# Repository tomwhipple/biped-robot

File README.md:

# Biped

A ~46 cm (to the deck; 56 cm to the top of the head) 3D-printed **bipedal
robot**: 17 serial-bus servos — six per leg, a neck, and two 2-DOF arms that
push it back up after a fall — an ESP32 running the 50 Hz control loop, and a
Raspberry Pi with a head camera. It is designed to walk by lifting a foot
clear of the ground: a static single-foot stance exists with 30 mm of margin,
and an open-loop gait in simulation, run against the measured actuation chain,
proves the body has the margins. The robot itself is driven by a
reinforcement-learning policy on the ESP32: standing, balance, stepping,
turning and walking all come from it.

**Status:** the legs are built (the 12 leg servos and the control board; no
pack, Pi, head, neck or arms yet), and a trained legs policy —
`robot_legs_walk16_act_s128r24`, a distilled (128, 128) student on the v6 legs
plant — runs on the ESP32 and holds the robot standing. Walking on the floor
is not yet shown on hardware; the milestones are marching in place with full
weight transfer, then a stride, then the full command volume. The CAD for the whole robot is complete and
passes its swept-ROM interference gate; the design passes simulation Gates
A–D, and walking and get-ups train on the robot's plants.
Where everything stands: [DESIGN.md](DESIGN.md) §12–13 and the GitHub issues.

*Loosely inspired by the [Bimo Project](https://github.com/mekion/the-bimo-project);
an independent design built from servo datasheet dimensions, not reverse-engineered
parts.*

## Try it

Everything below runs on a laptop with no robot and no GPU.

```bash
python -m venv .venv && source .venv/bin/activate    # direnv does this via .envrc
pip install -r requirements.txt
make help                                  # every build, run and test target

# look at the robot: drag its joints under gravity, push it over (native Qt window)
make puppet                                # standing; ARGS="--pose supine" or "--pose prone"
make sim                                   # the plant in MuJoCo's viewer

# the design gates, on the robot's plant
python sim/static_gait.py --render build/v6/movies/walk.mp4   # the open-loop walk
python sim/gate_no3250.py walk             # the walk across the gate cases

# regenerate the printable parts from the parametric source, then gate them
make cad                                   # every part whose source changed: STL (build/v6/stl), STEP and mass rollup (build/v6)
make check-cad                             # swept-ROM interference, must PASS
make slice                                 # OrcaSlicer projects + gcode, in build/v6/gcode

# the test gates (also run by the pre-push hook)
make test                                  # the firmware's pure modules under ASan/UBSan + the consoles, then
                                           # pytest tests/ (~4 min) and the SIL suite
```

The console drives a simulated robot over the real command protocol, and
`make console ARGS="--host <robot-ip>"` drives a real one:

```bash
brew install glfw && make console
#   SIM: pick a run, Start; [a] arm, arrows to walk, PgUp/PgDn to turn
```

That is `bimo_gui` (Dear ImGui), the console for hardware sessions. The Qt
operator console that replaces it, `link/bimo_console.py` (built by
`make -C firmware/host console`), opens with `make qtconsole`; it has not yet
run a hardware session ([docs/console.md](docs/console.md)).

**Trained policies are not in the repo.** They are local artifacts under
`sim/runs/` (gitignored); [docs/training.md](docs/training.md) walks the pipeline
from the physics model to the weights compiled into the firmware. Training
wants an NVIDIA GPU; the referee, distillation and export run on a laptop.

## Where to read next

| | |
|---|---|
| [DESIGN.md](DESIGN.md) | **the design**: requirements, kinematics, servos, body, get-up, validation, open decisions, build sequence |
| [cad/README.md](cad/README.md) · [cad/PRINT_LIST.md](cad/PRINT_LIST.md) | the parametric CAD, and what to print and how |
| [docs/bom.md](docs/bom.md) · [docs/assembly.md](docs/assembly.md) | what to buy, and how to put it together |
| [docs/wiring.md](docs/wiring.md) · [docs/servo-map.md](docs/servo-map.md) · [docs/bringup.md](docs/bringup.md) | power and electrical, servo IDs and calibration, bare board to first arm |
| [firmware/README.md](firmware/README.md) · [docs/firmware-design.md](docs/firmware-design.md) | what runs on the ESP32 |
| [docs/control-channel.md](docs/control-channel.md) | the wireless command protocol and its failsafe |
| [docs/console.md](docs/console.md) | the Qt operator console: roles, the stops, input, the tabs, the gamepad, its ports |
| [docs/wifi-cli.md](docs/wifi-cli.md) | the bench CLI over Wi-Fi: provisioning, what is refused, the threat model |
| [docs/training.md](docs/training.md) · [docs/sil-harness.md](docs/sil-harness.md) | how a policy is trained, refereed and deployed |
| [AGENTS.md](AGENTS.md) | working practices: gates, branching, generated files, bench safety |
| [docs/design-v6/](docs/design-v6/README.md) | dated design records and the evidence behind DESIGN.md's numbers |
| [docs/archive/](docs/archive/README.md) | the project's history: the prototype, lessons learned, earlier studies |

## What's in here

```
cad/v6/     the robot's parametric CAD (build123d); cad/v6/dimensions_v6.py is the source of truth
cad/        shared CAD library (cad/common/), slicing and checks
sim/        the plants, design gates, open-loop gait and get-up; the CPU env (referee); sim/mjx/ (GPU training); sim/sil/
firmware/   the ESP32 target: the 50 Hz control loop, and its host test build
link/       the command channel: wire protocol, consoles, bench probes
tools/      sim <-> firmware exporters, and instruments that measure servos and the IMU
infra/      nightly training on the GPU box, burst compute
docs/       build, electrical, software and design records
```

## Hardware

15 × Feetech STS3215 (12 V) + 2 × STS3250 (hip rolls) · Waveshare General
Driver for Robots (ESP32, onboard IMU) · Raspberry Pi 4B + Camera Module 3 Wide · 3S 2200–2600 mAh LiPo ·
PETG prints + silicone rubber soles. Full list: [docs/bom.md](docs/bom.md).

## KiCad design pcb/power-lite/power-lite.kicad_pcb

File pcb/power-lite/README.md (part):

# Power lite: the robot's battery protection and power distribution

*The choices behind it are in
[2026-11-02-power-lite-options.md](../../docs/design-v6/2026-11-02-power-lite-options.md). It
is how the robot is powered. How to solder and wire it: [assembly.md](assembly.md); its
connectors and cables: [harness.md](harness.md).*

A 2-layer board, 97 × 64.5 mm, with through-hole parts only, soldered by hand. It carries:
- the pack's connectors;
- the solder pads for an off-the-shelf 3S BMS and for the main switch;
- the fuses;
- a relay that the E-stop drops;
- the servo distribution;
- the signals to the ESP32.

## How power flows

*The circuit as a wired drawing: `tools/draw_circuit.py`, with the same parts and nets as
`tools/parts.py`. The KiCad schematic carries the same nets as labels on every pin.*

```
pack XT60 (J1) ─ BMS (W1-W5, cuts the negative lead) ─ main switch (W6/W7) ─┬─ F2 3 A ─ J3 ─ General Driver H1 (and the Pi)
pack balance lead (J2) ─ BMS cell taps                                      ├─ F2 3 A ─ J11 E-stop NC ─ K1 coil ─ Q1 ─ GND
                                                                             └─ F1 15 A ─ K1 contact ─ SERVO+ ─ J4-J7
```

- **The BMS** is a ShillehTek CF-3SJH25A-C ($6.99, ships from the US).
  - It sits on wires: its B−, B3, B2 and B1+ pads go to W1, W3, W4 and W5, and its P− pad to
    W2.
  - It switches the negative lead, so the system ground is its P−. The pack's balance lead
    goes only to the BMS, through J2.
  - Its thresholds are not documented. **On the bench it has no under-voltage cut-off**: its
    output stayed on down to 2.13 V a cell
    ([2026-11-19 record](../../docs/design-v6/2026-11-19-power-lite-bms-bench.md)). So it does
    not protect the pack if the robot is left on, and a replacement is open (#207).
- **The main switch** is a 20 A panel toggle on W6 and W7, in the power bay's switch pod
  (#213). It is marked 20 A 125 VAC, with no DC rating: carrying 15 A is within it, but
  breaking DC under load is not rated. So turn it off only after the E-stop has dropped the
  servo rail, and it breaks only the logic's 1 A or so.
- **The servo rail** is fed through the TE 1-1414610-0 relay (K1; 70 A, operates at 7.2 V).
  - The relay's coil current, about 0.13 A, flows only while the E-stop's NC contact (J11) is
    closed and the ESP32 holds `SERVO_EN` high.
  - Pressing the E-stop drops the rail without firmware.
  - Until the ESP32 drives `SERVO_EN`, R2 holds Q1 off and the rail stays off.
- **The coil:** D1 clamps its turn-off. The relay's built-in 470 Ω alone would put about 63 V
  on Q1 (rated 40 V), and about −66 V on the E-stop and Q2's base when the E-stop opens.
  - TE warns that a coil diode slows the release and shortens the contact life (V23134 notes
    4 and 6).
  - The relay switches a few times a session, far inside its 10⁵-operation life, and the
    simulated release still takes only 5.3 ms.
- **The General Driver and the Pi** are fed through F2 and stay up through an E-stop.
- **Surge:** D2 and D3 (1.5KE16A) clamp the servo rail and the switched input. C1 (1000 µF)
  is the servo bulk.

## Connectors

| ref | what | part | pins |
|---|---|---|---|
| J1 | the pack | Amass XT60PW-M | 1 B− (angled side), 2 B+ |
| J2 | the pack's balance lead | JST B4B-XH-A | 1 B−, 2 cell 1+, 3 cell 2+, 4 B+ |
| J3 | General Driver H1 | JST B2B-XH-A | 1 LOGIC (+), 2 GND; the lead runs pin 1 to pin 1 |
| J4–J7 | servo branches: R leg, R upper, L leg, L upper | Molex 22-03-5035 | 1 data, 2 SERVO+, 3 GND (the General Driver's H5 order, "D V G"); data at the housing's bevelled corner, as on H5 |
| J8 | servo data from the General Driver's H5 | Molex 22-03-5035 | 1 data, 2 unconnected, 3 GND; data at the bevelled corner |
| J11 | the E-stop's NC contact | JST B2B-PH-K-S | 1 LOGIC, 2 to K1's coil; any latching switch (0.13 A) |
| J12 | control to the ESP32 | JST B8B-PH-K-S | 2 `SERVO_EN` (IO16), 3 GND, 5 `RAIL_V` (GPIO34), 6 `ESTOP_N` (IO4, with its internal pull-up on); 1, 4, 7, 8 unconnected |
| W1–W5 | the BMS | wire pads | W1 B−, W2 P− (system GND), W3 B3, W4 B2, W5 B1+ |
| W6/W7 | the main switch | wire pads | W6 pack B+, W7 switched (VIN) |

- **J1's plug faces out of the left edge.** The XT60's mating face overhangs the edge by 0.25 mm,
  with its pins 16.1 mm in. Ask the board house for no rail or panel on
  that edge.
- **J3 and J11 are different families** (XH and PH), so the two 2-pin leads cannot swap.
- **The ESP32's readings:**
  - `RAIL_V` is SERVO+ divided by 5.7, giving 2.21 V at 12.6 V.
  - `ESTOP_N` is an open collector (Q2), read by IO4 with its internal pull-up on.
    - It reads low while the E-stop is released, because Q2 conducts while the coil supply is up.
    - It reads high when the E-stop is pressed, the board is unpowered, F2 has blown, or the
      lead is unplugged. Every failure reads as stop.
  - C2 (100 nF) filters `RAIL_V` for the ADC.
- **J3 and J4–J8 follow the General Driver's pin orders**: the cables and checks P1–P4 are in
  [harness.md](harness.md).
- **J4–J8 are keyed like H5.** A stock servo lead joins its two housings' bevelled corners, and
  H5's D is at its bevelled corner, so each header's bevelled corner is at pin 1 (data). The
  board's footprint (`power-lite.pretty/Molex_SPOX_5267-03A_1x03_P2.50mm_Vertical_KeyPin1`) is
  KiCad's stock Mini-SPOX with the housing turned 180° on the same pads.

## The firmware

`rail` reads the state, `SERVO_EN`, `RAIL_V`, `ESTOP_N`, the fault, the last drop and why the
ESP32 last reset (power-on, brown-out, panic, a watchdog), over Wi-Fi too: a reboot that
a Wi-Fi session saw only as "session lost" can be told apart afterwards.

A robot with this board runs its own image: `make firmware POWER_LITE=1`, in
`build/firmware-powerlite` (it combines with `POLICY=`). It is a build option because on
a robot without the board IO4 is the WS2812 net and IO16 goes nowhere, and a floating
`ESTOP_N` must read as stop, so nothing can detect the board at run time: this image
would never arm that robot. A default image does not touch these pins.

The logic is `firmware/components/railguard` (its header has the derivations), and the
hardware half `firmware/main/power_rail.cpp`.

- **Arming.** `ESTOP_N` must be low, and the rail must have fallen below 8 V since it was
  last on. `SERVO_EN` goes high; `RAIL_V` must pass 8 V within 250 ms; the servos get
  500 ms to boot. Only then is the bus used. On a timeout `SERVO_EN` drops and the fault
  is reported.
- **The servos are off until something asks.**
  - An arm (`run`, an ARM edge) powers the rail itself. So do `home`, the wireless reset
    and the fall pick-up's autohome, which turn it off again when the home has released
    torque.
  - Bench work (`scan`, `pos`, `cal`, `pose`) needs `rail on` first, over
    the tether or Wi-Fi (`tools/wcli.py rail on`; Tom 2026-11-21, see the
    [record](../../docs/design-v6/2026-11-21-rail-over-wifi.md)). Without it those commands
    say so. Scripts in `tools/` that talk to the servos need it too. `rail panic` and
    `rail clear` stay on the tether, and every interlock below applies to a Wi-Fi line as it
    does to a tether one.
  - No servo is read at boot: the gain check is the arm's, with the rail up, and it
    re-applies the servos' RAM settings, which a power cycle loses.
- **`SERVO_EN` drops on:** a disarm (`bench`, ARM off), a hard operator stop in any mode,
  the link's RELAX and `ESTOP`, the pack guard's safe state, a fall, `ESTOP_N` going high,
  and the rail collapsing below 7 V for 500 ms. Each of those ends a run: `RAIL_DOWN` in
  the beacon, or `DISARMED_FALL` / `DISARMED_STOP`. A flail-guard or soft-stop hold keeps
  the rail, because it holds with torque on, until the bench home has released it, or
  `release` does. Benched, the pack guard's trip drops nothing: until `batt reset` it
  refuses `rail on` and a home, and an arm goes limp at once, but a rail already on stays.
- **A commander's `ESTOP` press drops it benched too**, whoever powered it. The press is
  the edge: the frame where the flag goes up, or the first one with it after 500 ms with no
  frame. The rail is refused until the commander lets go or for 500 ms, whichever is first.
  A flag still held after that blocks nothing, so a console left E-stopped needs nobody at
  it (Tom 2026-11-19): **RESET SERVOS** from it, `rail on` and the pick-up's autohome all
  power the rail, and the held flag does not take it back. A fresh press does. An ARM edge
  in a frame with `ESTOP` is refused.
- **A rail the firmware powered goes when its reason does**: a home that ends or fails, and `release` of all the servos, each of which has released torque. A soft stop during a
  home holds torque, as on a default image, so the rail stays until the next `home` ends,
  `release` or `bench`. A typed `rail on` stays until `rail off`, `bench` or a drop.
- **Nothing brings the rail back by itself.**
  - `ESTOP_N` going high latches. `bench` clears the latch from the tether or over Wi-Fi
    (it is on the Wi-Fi allowlist), so after a power cycle `bench`, `rail on` works the same on
    both. Back at RUN, the rail stays off and an arm is refused
    until a disabled command arrives: `bench`, or a frame with `ENABLE`, `ARM` and `ESTOP`
    clear. Then it takes a fresh arm. So: RUN, disarm, arm.
  - Except the pick-up autohome, as on a default image (Tom 2026-11-19): upright and still
    for 1 s after a fall, it powers the rail, homes, and drops the rail again. `fall
    autohome off` turns it off. Refused (E-stop latched, a fault), it says why and the fall
    latch stands. A latch clears when a home starts, not when one is refused.
- **A welded K1.** `RAIL_V` above 8 V with `SERVO_EN` low, for 8 s with no new low of
  150 mV, raises the stuck-rail fault. It also runs from the first sample after boot. A
  rail that is still falling never raises it, however slowly: without servos it takes
  2.9 s to reach 8 V through LED2, and 31 s if LED2 is open. The fault refuses arming, and
  `rail clear` is refused until the rail has fallen.
- **A reset.** A panic or a restart takes `SERVO_EN` low first: the linker wraps the panic
  handler and `esp_restart_noos`, because that CPU reset alone leaves the ESP32's GPIOs as
  they were. A brown-out is a full system reset, which leaves the pin to R2. The task
  watchdog panics in this image (in a default image it only warns), so a
  wedged control loop drops the rail within 1 s. The robot goes limp where it is, and comes
  back benched with the rail off. An ARM bit held high makes no edge, so it does not re-arm.
- **Telemetry.** `stat` and `rail` print the state, `SERVO_EN`, `RAIL_V`, `ESTOP_N`, the
  latch, the fault and the last drop's reason; every change prints and is a flight-recorder
  event (`rail`). The beacon's power block (asked for with `PWR`;
  [control-channel.md](../../docs/control-channel.md#the-power-block)) carries `RAIL_V`,
  `ESTOP_N`, `SERVO_EN` and the E-stop latch, with the INA219's pack voltage and the pack
  guard's level. `vbat` (the servos' register 62) reads 0 with the rail off; the pack
  guard then runs on the INA219 alone.

### The bench check, with the ESP32

Bring-up step 2 below, the ESP32 in place of the 3.3 V on J12.2: it needs Part 2 of
[bringup.md](bringup.md) and no BMS. One session covers the rail (#218, steps 1-8) and the
pack sense (#109, steps 9-12). No servo is connected, so filming is optional (AGENTS.md).

**Set up**, supply off:
- The supply as in bringup.md 2.1: 12.0 V, limit 0.5 A, + to W7, − to W2. Both fuses in, the
  J11 jumper in (or the E-stop lead at RUN). No BMS, no pack, J4–J8 empty.
- The breadboard rig off. The J12 lead on the General Driver: P3 pin 4, P3 pin 3, H3 pin 4 and
  H2 pin 1 ([harness.md](harness.md#j12-control-to-the-esp32)).
- **The J3 lead into the General Driver's H1** (harness check P3), its switch SW1 on. Then the
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
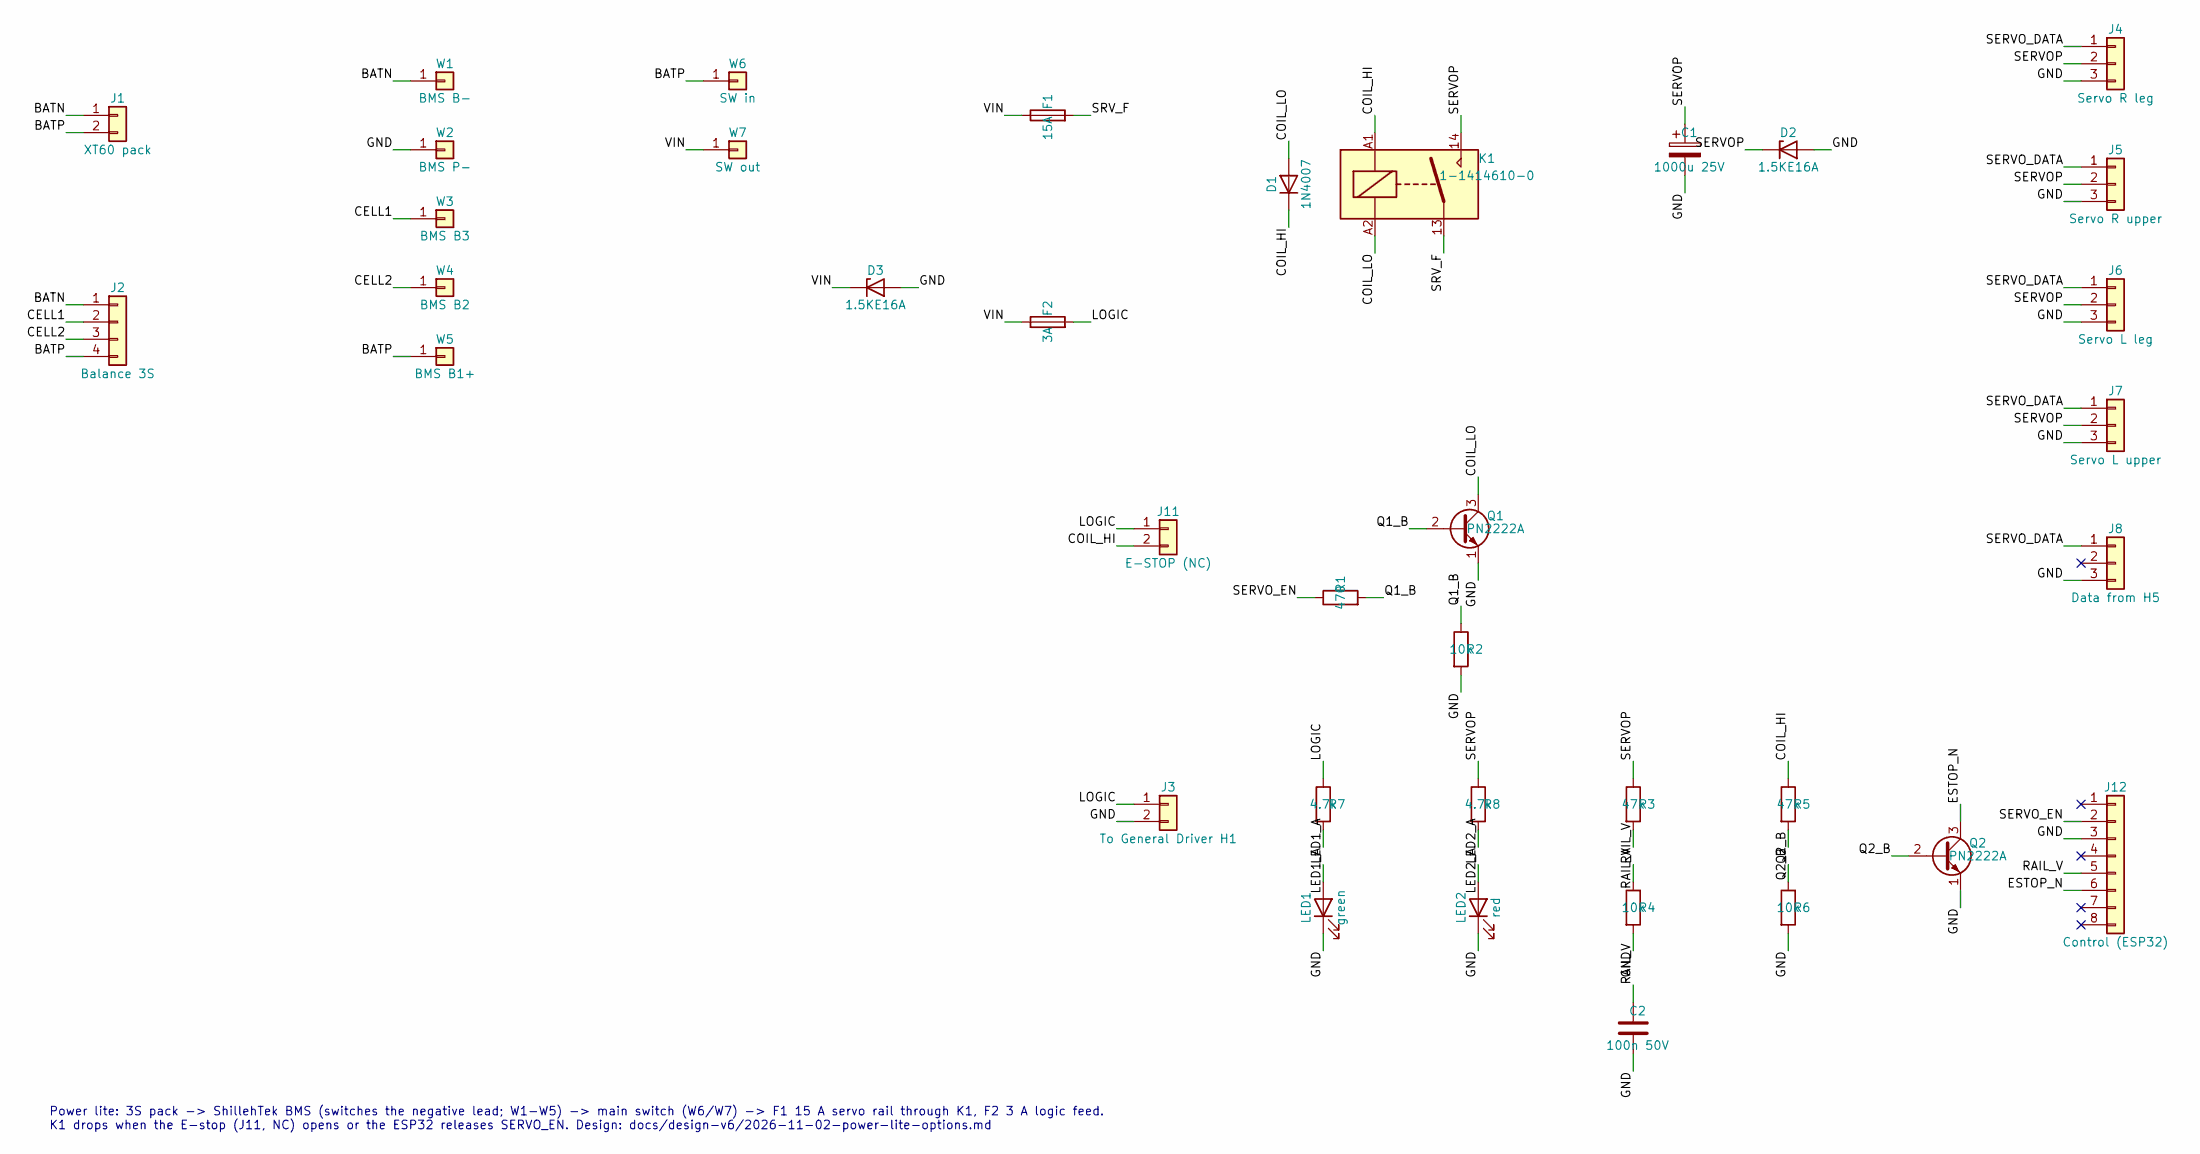
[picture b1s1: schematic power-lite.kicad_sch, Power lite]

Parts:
C1: 1000u 25V; CP_Radial_D10.0mm_P5.00mm; MPN Panasonic EEU-FR1E102
C2: 100n 50V; C_Disc_D5.0mm_W2.5mm_P5.00mm; MPN KEMET C322C104K5R5TA
D1: 1N4007; D_DO-41_SOD81_P10.16mm_Horizontal; MPN Good-Ark 1N4007
D2, D3: 1.5KE16A; D_DO-201_P15.24mm_Horizontal; MPN Littelfuse 1.5KE16A
F1: 15A; Fuseholder_Blade_Mini_Keystone_3568; MPN Keystone 3568
F2: 3A; Fuseholder_Blade_Mini_Keystone_3568; MPN Keystone 3568
J1: XT60 pack; AMASS_XT60PW-M_1x02_P7.20mm_Horizontal_EdgeMount; MPN Amass XT60PW-M
J2: Balance 3S; JST_XH_B4B-XH-A_1x04_P2.50mm_Vertical; MPN JST B4B-XH-A
J3: To General Driver H1; JST_XH_B2B-XH-A_1x02_P2.50mm_Vertical; MPN JST B2B-XH-A
J4: Servo R leg; Molex_SPOX_5267-03A_1x03_P2.50mm_Vertical_KeyPin1; MPN Molex 22-03-5035
J5: Servo R upper; Molex_SPOX_5267-03A_1x03_P2.50mm_Vertical_KeyPin1; MPN Molex 22-03-5035
J6: Servo L leg; Molex_SPOX_5267-03A_1x03_P2.50mm_Vertical_KeyPin1; MPN Molex 22-03-5035
J7: Servo L upper; Molex_SPOX_5267-03A_1x03_P2.50mm_Vertical_KeyPin1; MPN Molex 22-03-5035
J8: Data from H5; Molex_SPOX_5267-03A_1x03_P2.50mm_Vertical_KeyPin1; MPN Molex 22-03-5035
J11: E-STOP (NC); JST_PH_B2B-PH-K_1x02_P2.00mm_Vertical; MPN JST B2B-PH-K-S
J12: Control (ESP32); JST_PH_B8B-PH-K_1x08_P2.00mm_Vertical; MPN JST B8B-PH-K-S
K1: 1-1414610-0; TE_PowerRelay_F7_PCB; MPN TE 1-1414610-0
LED1: green; LED_D3.0mm; MPN Kingbright WP710A10GD
LED2: red; LED_D3.0mm; MPN Kingbright WP710A10ID
Q1, Q2: PN2222A; TO-92_Inline_Wide; MPN onsemi PN2222A
R1: 470; R_Axial_DIN0207_L6.3mm_D2.5mm_P10.16mm_Horizontal; MPN Yageo MFR-25FBF52-470R
R2, R4, R6: 10k; R_Axial_DIN0207_L6.3mm_D2.5mm_P10.16mm_Horizontal; MPN Yageo MFR-25FBF52-10K
R3, R5: 47k; R_Axial_DIN0207_L6.3mm_D2.5mm_P10.16mm_Horizontal; MPN Yageo MFR-25FBF52-47K
R7, R8: 4.7k; R_Axial_DIN0207_L6.3mm_D2.5mm_P10.16mm_Horizontal; MPN Yageo MFR-25FBF52-4K7
W1: BMS B-; SolderWire-2sqmm_1x01_D2mm_OD3.9mm
W2: BMS P-; SolderWire-2sqmm_1x01_D2mm_OD3.9mm
W3: BMS B3; SolderWire-0.5sqmm_1x01_D0.9mm_OD2.1mm
W4: BMS B2; SolderWire-0.5sqmm_1x01_D0.9mm_OD2.1mm
W5: BMS B1+; SolderWire-0.5sqmm_1x01_D0.9mm_OD2.1mm
W6: SW in; SolderWire-2sqmm_1x01_D2mm_OD3.9mm
W7: SW out; SolderWire-2sqmm_1x01_D2mm_OD3.9mm

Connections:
/BATN: J1.1, J2.1, W1.1
/BATP: J1.2, J2.4, W5.1, W6.1
/CELL1: J2.2, W3.1
/CELL2: J2.3, W4.1
/COIL_HI: D1.1 (K), J11.2, K1.A1, R5.1
/COIL_LO: D1.2 (A), K1.A2, Q1.3 (C)
/ESTOP_N: J12.6, Q2.3 (C)
/GND: C1.2, C2.2, D2.2 (A), D3.2 (A), J3.2, J4.3, J5.3, J6.3, J7.3, J8.3, J12.3, LED1.1 (K), LED2.1 (K), Q1.1 (E), Q2.1 (E), R2.2, R4.2, R6.2, W2.1
/LED1_A: LED1.2 (A), R7.2
/LED2_A: LED2.2 (A), R8.2
/LOGIC: F2.2, J3.1, J11.1, R7.1
/Q1_B: Q1.2 (B), R1.2, R2.1
/Q2_B: Q2.2 (B), R5.2, R6.1
/RAIL_V: C2.1, J12.5, R3.2, R4.1
/SERVOP: C1.1, D2.1 (K), J4.2, J5.2, J6.2, J7.2, K1.14, R3.1, R8.1
/SERVO_DATA: J4.1, J5.1, J6.1, J7.1, J8.1
/SERVO_EN: J12.2, R1.1
/SRV_F: F1.2, K1.13
/VIN: D3.1 (K), F1.1, F2.1, W7.1

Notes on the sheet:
Power lite: 3S pack -> ShillehTek BMS (switches the negative lead; W1-W5) -> main switch (W6/W7) -> F1 15 A servo rail through K1, F2 3 A logic feed. K1 drops when the E-stop (J11, NC) opens or the ESP32 releases SERVO_EN. Design: docs/design-v6/2026-11-02-power-lite-options.md

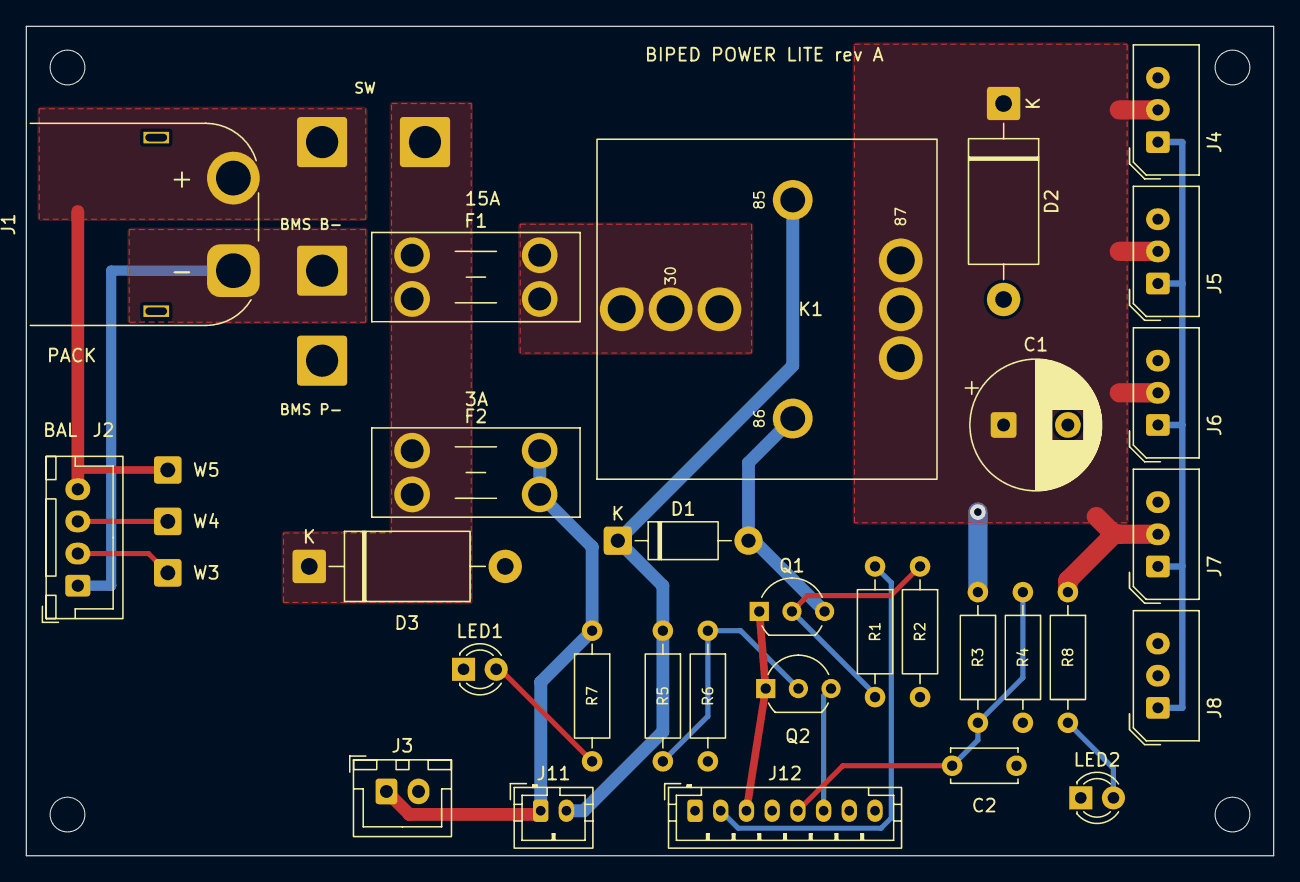
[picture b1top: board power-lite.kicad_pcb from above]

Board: 2 copper layers, 97.0 x 64.5 mm, 41 parts (0 on the bottom side), 19 nets.

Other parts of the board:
H1, H2, H3, H4: M2.5; MountingHole_2.7mm_M2.5

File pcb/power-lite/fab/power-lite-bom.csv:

"Refs","Value","Footprint","MPN","Datasheet","Qty"
"C1","1000u 25V","Capacitor_THT:CP_Radial_D10.0mm_P5.00mm","Panasonic EEU-FR1E102","https://industrial.panasonic.com/cdbs/www-data/pdf/RDF0000/A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","1"
"C2","100n 50V","Capacitor_THT:C_Disc_D5.0mm_W2.5mm_P5.00mm","KEMET C322C104K5R5TA","","1"
"D1","1N4007","Diode_THT:D_DO-41_SOD81_P10.16mm_Horizontal","Good-Ark 1N4007","https://goodarksemi.com/docs/datasheets/general_purpose_rect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","1"
"D2,D3","1.5KE16A","Diode_THT:D_DO-201_P15.24mm_Horizontal","Littelfuse 1.5KE16A","https://www.littelfuse.com/media?resourcetype=datasheets&ite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","2"
"F1","15A","Fuse:Fuseholder_Blade_Mini_Keystone_3568","Keystone 3568","https://www.keyelco.com/userAssets/file/M65p73.pdf","1"
"F2","3A","Fuse:Fuseholder_Blade_Mini_Keystone_3568","Keystone 3568","https://www.keyelco.com/userAssets/file/M65p73.pdf","1"
"J1","XT60 pack","power-lite:AMASS_XT60PW-M_1x02_P7.20mm_Horizontal_EdgeMount","Amass XT60PW-M","https://www.amass.com.cn/pdf/XT60PW.pdf","1"
"J2","Balance 3S","Connector_JST:JST_XH_B4B-XH-A_1x04_P2.50mm_Vertical","JST B4B-XH-A","https://www.jst-mfg.com/product/pdf/eng/eXH.pdf","1"
"J3","To General Driver H1","Connector_JST:JST_XH_B2B-XH-A_1x02_P2.50mm_Vertical","JST B2B-XH-A","https://www.jst-mfg.com/product/pdf/eng/eXH.pdf","1"
"J4","Servo R leg","Connector_Molex:Molex_SPOX_5267-03A_1x03_P2.50mm_Vertical","Molex 22-03-5035","https://www.molex.com/en-us/products/part-detail/22035035","1"
"J5","Servo R upper","Connector_Molex:Molex_SPOX_5267-03A_1x03_P2.50mm_Vertical","Molex 22-03-5035","https://www.molex.com/en-us/products/part-detail/22035035","1"
"J6","Servo L leg","Connector_Molex:Molex_SPOX_5267-03A_1x03_P2.50mm_Vertical","Molex 22-03-5035","https://www.molex.com/en-us/products/part-detail/22035035","1"
"J7","Servo L upper","Connector_Molex:Molex_SPOX_5267-03A_1x03_P2.50mm_Vertical","Molex 22-03-5035","https://www.molex.com/en-us/products/part-detail/22035035","1"
"J8","Data from H5","Connector_Molex:Molex_SPOX_5267-03A_1x03_P2.50mm_Vertical","Molex 22-03-5035","https://www.molex.com/en-us/products/part-detail/22035035","1"
"J11","E-STOP (NC)","Connector_JST:JST_PH_B2B-PH-K_1x02_P2.00mm_Vertical","JST B2B-PH-K-S","https://www.jst-mfg.com/product/pdf/eng/ePH.pdf","1"
"J12","Control (ESP32)","Connector_JST:JST_PH_B8B-PH-K_1x08_P2.00mm_Vertical","JST B8B-PH-K-S","https://www.jst-mfg.com/product/pdf/eng/ePH.pdf","1"
"K1","1-1414610-0","power-lite:TE_PowerRelay_F7_PCB","TE 1-1414610-0","https://www.te.com/commerce/DocumentDelivery/DDEController?A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","1"
"LED1","green","LED_THT:LED_D3.0mm","Kingbright WP710A10GD","https://www.kingbrightusa.com/images/catalog/SPEC/WP710A10GD.pdf","1"
"LED2","red","LED_THT:LED_D3.0mm","Kingbright WP710A10ID","https://www.kingbrightusa.com/images/catalog/SPEC/WP710A10ID.pdf","1"
"Q1,Q2","PN2222A","Package_TO_SOT_THT:TO-92_Inline_Wide","onsemi PN2222A","https://www.onsemi.com/pdf/datasheet/pn2222a-d.pdf","2"
"R1","470","Resistor_THT:R_Axial_DIN0207_L6.3mm_D2.5mm_P10.16mm_Horizontal","Yageo MFR-25FBF52-470R","https://www.yageo.com/upload/media/product/productsearch/dat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","1"
"R2,R4,R6","10k","Resistor_THT:R_Axial_DIN0207_L6.3mm_D2.5mm_P10.16mm_Horizontal","Yageo MFR-25FBF52-10K","https://www.yageo.com/upload/media/product/productsearch/dat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","3"
"R3,R5","47k","Resistor_THT:R_Axial_DIN0207_L6.3mm_D2.5mm_P10.16mm_Horizontal","Yageo MFR-25FBF52-47K","https://www.yageo.com/upload/media/product/productsearch/dat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","2"
"R7,R8","4.7k","Resistor_THT:R_Axial_DIN0207_L6.3mm_D2.5mm_P10.16mm_Horizontal","Yageo MFR-25FBF52-4K7","https://www.yageo.com/upload/media/product/productsearch/dat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","2"

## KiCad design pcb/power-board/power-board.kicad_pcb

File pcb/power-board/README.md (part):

# Power board

The robot's custom power board, as designed in
[docs/design-v6/2026-10-06-power-circuit.md](../../docs/design-v6/2026-10-06-power-circuit.md)
§5. Open `power-board.kicad_pro` in KiCad 10. [`power-board.pdf`](power-board.pdf)
is a plot of the schematic for reading without KiCad. [harness.md](harness.md) gives every
cable and connector to the rest of the robot.

**State: schematic and layout rev B, verified on paper, not ordered.**
- **Clean:** ERC and DRC report no violations.
- **Checked:** the simulations, footprint checks and copper analysis are in
  [the verification record](../../docs/design-v6/2026-10-07-power-board-verification.md).
- **In stock:** every part has a manufacturer datasheet. J1 (the XT60) and F1/F2's fuse
  holders are left off the assembly order and soldered by hand
  ([quote record](../../docs/design-v6/2026-10-24-power-board-quote.md)).
- **Simulated whole:** the drawn netlist in ngspice with pin models of U1 and U2, every
  combination of the board's inputs, timed sequences, faults and sweeps
  ([the simulation record](../../docs/design-v6/2026-10-24-power-board-full-simulation.md),
  code in `pbsim/board/`, `make pbfull`), with a pin-by-pin datasheet
  [audit](../../docs/design-v6/2026-10-24-power-board-pin-audit.md) and a
  [layout review](../../docs/design-v6/2026-10-24-power-board-layout-review.md). Rev B
  carries their board changes, and the campaign re-run on it
  ([rev B record](../../docs/design-v6/2026-10-29-power-board-rev-b.md)).
- **Open:** a firm quote, and the physical checks P1–P7 ([harness.md](harness.md)), come
  before ordering. The outline and mounting holes wait on the torso redesign (#108).

## What is on it

| block | parts | function |
|---|---|---|
| pack input | J1 (XT60, right-angle), J2 (3S balance, JST XH), F1 (15 A MINI blade), R1 (1 mΩ) | the pack, a fuse for a hard short, and the coulomb-counter sense resistor in the negative lead |
| cell protection and main switch | U1 TI BQ76922 and its passives | per-cell cut-off without firmware; cells, current and charge over I²C (0x08); POWER wakes it on TS2; KILL (RST_SHUT) shuts it down |
| high-side FETs | Q1 (CHG), Q2 (DSG) CSD17556Q5B; gate networks; Q4 clamp | the BQ76922EVM topology, copied from TI's EVM schematic (SLVU957A): back-to-back FETs, 10 MΩ and 16 V zeners gate to source, a 4.7 kΩ turn-off path on DSG, and Q4 holding DSG off if PACK+ swings below ground |
| servo-rail switch | U2 TI TPS48111-Q1, Q3 CSD17556Q5B, R24 (2 mΩ) | soft start by gate slew, about 40 ms; overcurrent 20 A, latching off after 10 ms; short circuit at 40 A; the E-stop's NC contact in the EN/UVLO feed; SERVO_EN on INP; remote temperature diode Q5 at Q3 |
| servo distribution | J4–J7 (Molex 5267 3-pin), J8 (data in), C21 (1000 µF) | four branches; DATA and GND from the General Driver's H5, V+ from the switched rail |
| logic feed | F2 (3 A MINI blade fuse in a Keystone 3568 holder, replaceable by hand), J3 (JST XH 2-pin) | PACK+ to the General Driver's H1 |
| control | J9 (I²C, JST PH 4-pin), J12 (control, JST PH 8-pin), J10 (POWER, JST PH 2-pin), J11 (E-STOP, JST ZH 4-pin) | I²C and 3V3 to the General Driver's P1; KILL, SERVO_EN, PWR_INT_N, ESTOP_N, RAIL_V, SERVO_IMON and SERVO_FLT_N to the ESP32; the two buttons on the torso shell |

Component values follow the datasheets' application sections: BQ76922 (SLUSE86A §8.2,
and the BQ76922EVM schematic) and TPS4811-Q1 (SLUSEE5E §8.3, §9.2–9.3). TI's TPS4811-Q1
design calculator (SLURB09) confirms the servo-rail switch values.

## The board

**97 × 64.5 mm, four layers, 1.6 mm, ENIG.** The stackup is in the board file, so the
Gerber job file carries it.
- **Copper:** 1 oz (35 µm) on every layer, with a 1.04 mm core so the board stays 1.6 mm.
  The verification record's copper analysis (C11) finds 1 oz enough: 0.66 mΩ on the main
  path, 0.26 W at 20 A, and the copper is not the thermal limit. 2 oz outer at the 6/6 mil
  this board needs was most of the bare-board price (record 2026-10-07 and
  [2026-10-24-power-board-quote.md](../../docs/design-v6/2026-10-24-power-board-quote.md)).
- **Parts:** every part is on the top side. The through-hole parts are J1–J12, F1, F2 and
  C21. J1, F1 and F2 are do-not-populate: soldered by hand after assembly.

| layer | use |
|---|---|
| F.Cu | parts, signals, and the pours of the power path |
| In1.Cu | GND plane |
| In2.Cu | GND plane, with a BAT− island under the BQ76922 block (its VSS); the island takes in J1's BAT− pin |
| B.Cu | GND pour, signals, and copies of the BAT+, FBAT, PACK+ and SERVO+ pours stitched to the top |

**Placement.**
- **Power path:** J1 is a right-angle XT60 whose mating face is flush with the left edge.
  From it the power path runs along the top edge, left to right: F1, Q1 and Q2 drain to
  drain, R24, Q3, then SERVO+ around C21. J1 and J2 also take a bench supply instead of
  the pack, through the supply tether ([harness.md](harness.md)).
- **Servo headers:** a 2.6 mm SERVO+ strip runs down between the data and GND columns of the
  servo headers J4–J8 on the right edge.
- **Blocks:** the BQ76922 block sits under the left half, with the balance lead J2 above it.
  The TPS48111 block sits under R24 and Q3. The DSG gate network is above the strip.
- **Logic feed:** F2's holder and J3 are on a strip along the top edge. PACK+ copper runs up
  to F2's input, so the fuse can be pulled and replaced from above.
- **Control connectors:** J10, J9, J12 and J11 are along the bottom edge. J11 is a JST ZH,
  a family no other lead on the board uses, so the I²C lead cannot go into the E-stop's
  header.
- **PACK+ bulk:** C24–C27, 4 × 10 µF as two series pairs, and the bleed R41 sit above R24.

**High current.**
- **Pours:** every pad on the 15–20 A path sits in one solid pour per net, on top, with a
  copy on the bottom where the parts allow it. A script check confirms each pour fills as one
  piece covering all its pads.
- **Gate exits:** Q2's gate leaves through a via inside its pour's notch and crosses no
  pour. Q3's gate pad carries R43 (a 0 Ω placeholder for a gate resistor) and D10 (the
  15 V clamp to its source); from R43 the gate net runs on B.Cu under Q3, where the bottom
  is GND, to R28: about 10 mm.
- **Solid joints:** Q1–Q3, R1 and R24 join their pours solid. So do the ground pins of the
  through-hole connectors and C21: the servo returns carry amps, and thin thermal spokes would
  starve. That makes those pins harder to hand-solder.
- **R1's ground end** sits in a pour that covers its pad and reaches the planes through
  twenty 0.4 mm vias.

**Sensing.**
- **Kelvin traces:** SRP and SRN (through R7 and R8) leave R1's pads on their inner edges
  and touch nothing else. CS+ (through R25 and R26) and CS− leave R24's pads the same way.
- **Temperature:** Q5, the TPS48111's temperature diode, sits against Q3. RT1, the
  BQ76922's TS1 thermistor, sits under Q1 and Q2.

**Ground.** Every GND and BAT− SMD pad has its own via into its plane. GND stitching vias
on a 3 mm grid tie the planes and the bottom pour together.

**Rules.**
- Tracks and clearance: 0.15 mm minimum.
- Signal tracks: 0.2 mm by default; the logic feed is 1.2 mm.
- Vias: 0.6 mm with 0.3 mm drill.

These are within a standard 4-layer, 1 oz process at PCBWay or JLCPCB.

## Files

| file | what it is |
|---|---|
| `power-board.kicad_sch` | the schematic |
| `power-board.kicad_pcb` | the layout |
| `power-board.kicad_sym` | project symbols: BQ76922 (from TI's pin table, SLUSE86A table 5-1) and TPS48111-Q1 (SLUSEE5E table 5-1) |
| `power-board.pretty/TI_DGX0019A_VSSOP-19.kicad_mod` | the TPS48111-Q1 footprint, from TI's land pattern (drawing 4226944/A): 0.3 × 1.45 mm pads, 0.5 mm pitch, rows 4.4 mm apart, pad 16 left out |
| `power-board.pretty/TI_SON-8_5x6mm_P1.27mm_CSD17556Q5B.kicad_mod` | Q1–Q3, from TI's recommended PCB pattern and stencil (SLPS392D §7.2–7.3): drain columns at x −0.062 and +1.582, 0.766 × 0.508 mm finger apertures |
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
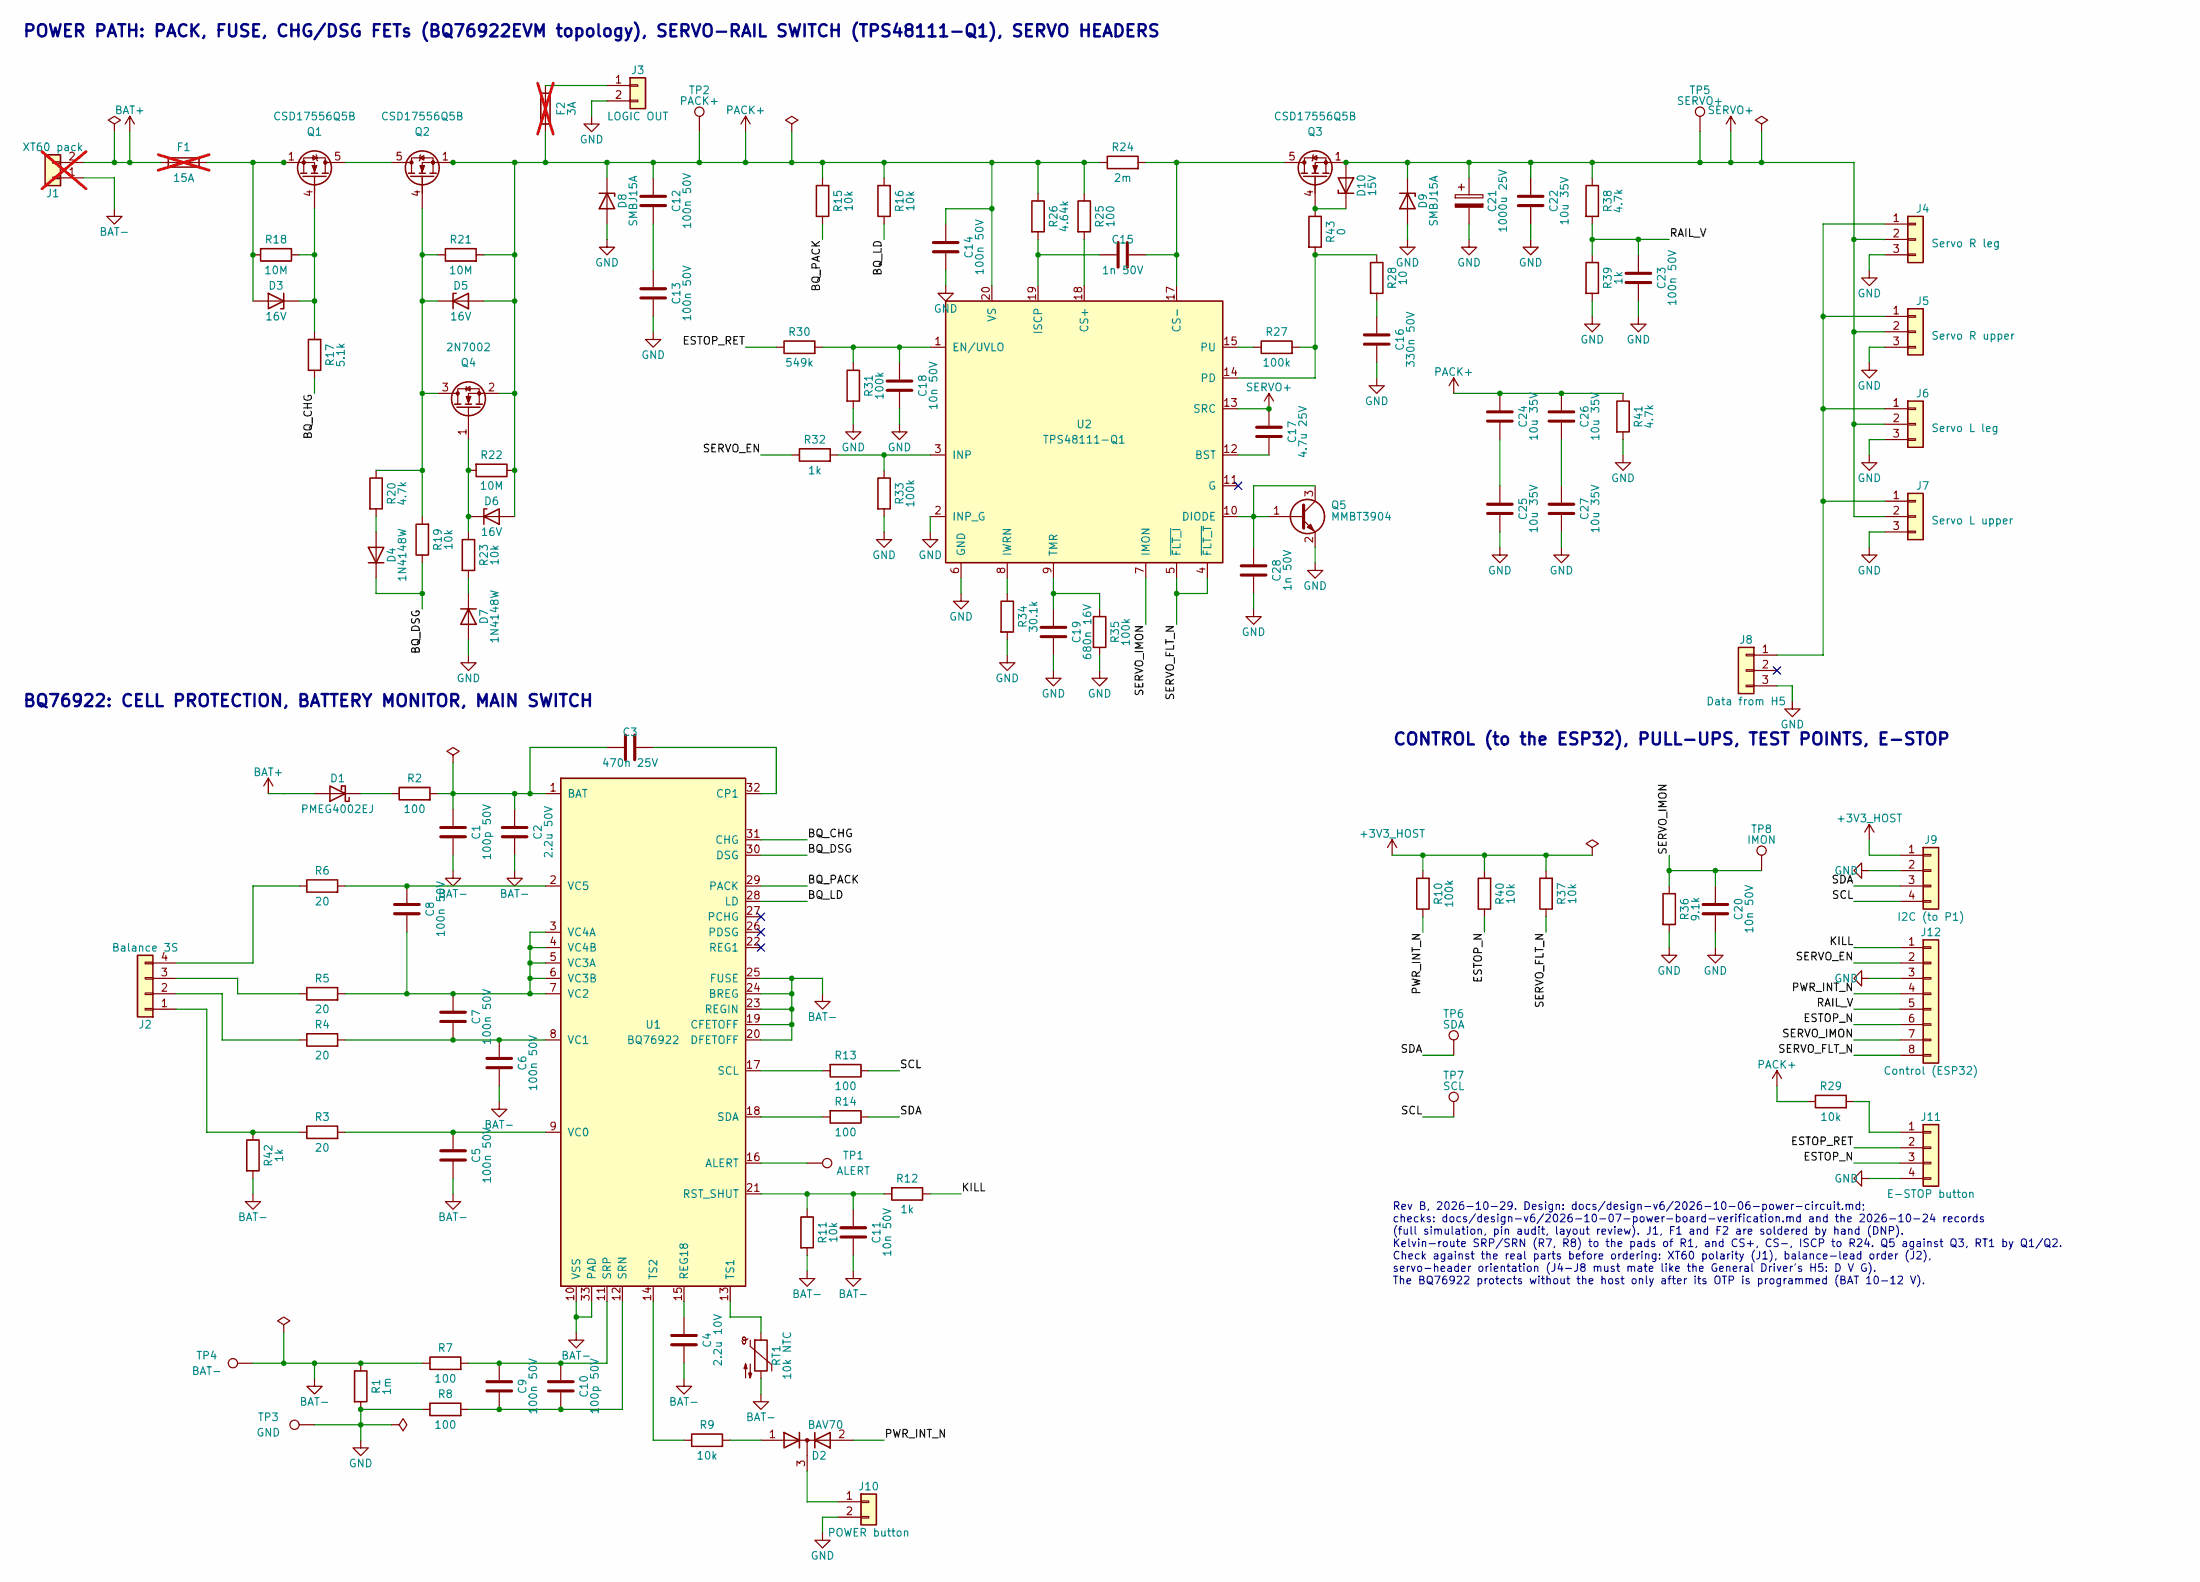
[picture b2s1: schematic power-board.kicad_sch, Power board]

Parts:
C1, C10: 100p 50V; C_0603_1608Metric; MPN Yageo CC0603JRNPO9BN101
C2: 2.2u 50V; C_1206_3216Metric; MPN KEMET C1206C225K5RACTU
C3: 470n 25V; C_0603_1608Metric; MPN Yageo CC0603KRX7R8BB474
C4: 2.2u 10V; C_0603_1608Metric; MPN Yageo CC0603KRX7R6BB225
C5, C6, C7, C8, C9, C14, C23: 100n 50V; C_0603_1608Metric; MPN Yageo CC0603KRX7R9BB104
C11, C18, C20: 10n 50V; C_0603_1608Metric; MPN Yageo CC0603KRX7R9BB103
C12, C13: 100n 50V; C_0805_2012Metric; MPN Yageo CC0805KRX7R9BB104
C15, C28: 1n 50V; C_0603_1608Metric; MPN Yageo CC0603JRNPO9BN102
C16: 330n 50V; C_0805_2012Metric; MPN Samsung CL21B334KBFNNNE
C17: 4.7u 25V; C_0805_2012Metric; MPN Samsung CL21B475KAFNNNE
C19: 680n 16V; C_0603_1608Metric; MPN Yageo CC0603KRX7R7BB684
C21: 1000u 25V; CP_Radial_D10.0mm_P5.00mm; MPN Panasonic EEU-FR1E102
C22, C24, C25, C26, C27: 10u 35V; C_1206_3216Metric; MPN Samsung CL31B106KLHNNNE
D1: PMEG4002EJ; D_SOD-323F; MPN Nexperia PMEG4002EJ-QX
D2: BAV70; SOT-23; MPN Diodes BAV70-7-F
D3, D5, D6: 16V; D_SOD-123; MPN Diodes MMSZ5246B-7-F
D4, D7: 1N4148W; D_SOD-123; MPN Diodes 1N4148W-7-F
D8, D9: SMBJ15A; D_SMB; MPN Bourns SMBJ15A
D10: 15V; D_SOD-123; MPN Diodes MMSZ5245B-7-F
F1: 15A; Fuseholder_Blade_Mini_Keystone_3568; MPN Keystone 3568; not fitted
F2: 3A; Fuseholder_Blade_Mini_Keystone_3568; MPN Keystone 3568; not fitted
J1: XT60 pack; AMASS_XT60PW-M_1x02_P7.20mm_Horizontal_EdgeMount; MPN Amass XT60PW-M; not fitted
J2: Balance 3S; JST_XH_B4B-XH-A_1x04_P2.50mm_Vertical; MPN JST B4B-XH-A
J3: LOGIC OUT; JST_XH_B2B-XH-A_1x02_P2.50mm_Vertical; MPN JST B2B-XH-A
J4: Servo R leg; Molex_SPOX_5267-03A_1x03_P2.50mm_Vertical; MPN Molex 22-03-5035
J5: Servo R upper; Molex_SPOX_5267-03A_1x03_P2.50mm_Vertical; MPN Molex 22-03-5035
J6: Servo L leg; Molex_SPOX_5267-03A_1x03_P2.50mm_Vertical; MPN Molex 22-03-5035
J7: Servo L upper; Molex_SPOX_5267-03A_1x03_P2.50mm_Vertical; MPN Molex 22-03-5035
J8: Data from H5; Molex_SPOX_5267-03A_1x03_P2.50mm_Vertical; MPN Molex 22-03-5035
J9: I2C (to P1); JST_PH_B4B-PH-K_1x04_P2.00mm_Vertical; MPN JST B4B-PH-K-S
J10: POWER button; JST_PH_B2B-PH-K_1x02_P2.00mm_Vertical; MPN JST B2B-PH-K-S
J11: E-STOP button; JST_ZH_B4B-ZR_1x04_P1.50mm_Vertical; MPN JST B4B-ZR(LF)(SN)
J12: Control (ESP32); JST_PH_B8B-PH-K_1x08_P2.00mm_Vertical; MPN JST B8B-PH-K-S
Q1, Q2, Q3: CSD17556Q5B; TI_SON-8_5x6mm_P1.27mm_CSD17556Q5B; MPN TI CSD17556Q5B
Q4: 2N7002; SOT-23; MPN Vishay 2N7002K-T1-GE3
Q5: MMBT3904; SOT-23; MPN Diodes MMBT3904-7-F
R1: 1m; R_2512_6332Metric; MPN Bourns CSS2H-2512R-1L00FE
R2, R7, R8, R13, R14, R25: 100; R_0603_1608Metric; MPN Yageo RC0603FR-07100RL
R3, R4, R5, R6: 20; R_0603_1608Metric; MPN Yageo RC0603FR-0720RL
R9, R11, R15, R16, R19, R23, R29, R37, R40: 10k; R_0603_1608Metric; MPN Yageo RC0603FR-0710KL
R10, R27, R31, R33, R35: 100k; R_0603_1608Metric; MPN Yageo RC0603FR-07100KL
R12, R32, R39, R42: 1k; R_0603_1608Metric; MPN Yageo RC0603FR-071KL
R17: 5.1k; R_0603_1608Metric; MPN Vishay CRCW06035K10FKEA
R18, R21, R22: 10M; R_0603_1608Metric; MPN Yageo RC0603FR-0710ML
R20, R38, R41: 4.7k; R_0603_1608Metric; MPN Yageo RC0603FR-074K7L
R24: 2m; R_2512_6332Metric; MPN Bourns CSS2H-2512K-2L00F
R26: 4.64k; R_0603_1608Metric; MPN Yageo RC0603FR-074K64L
R28: 10; R_0603_1608Metric; MPN Yageo RC0603FR-0710RL
R30: 549k; R_0603_1608Metric; MPN Yageo RC0603FR-07549KL
R34: 30.1k; R_0603_1608Metric; MPN Yageo RC0603FR-0730K1L
R36: 9.1k; R_0603_1608Metric; MPN Yageo RC0603FR-079K1L
R43: 0; R_0603_1608Metric; MPN Yageo RC0603JR-070RL
RT1: 10k NTC; R_0603_1608Metric; MPN Murata NCP18XH103F03RB
TP1: ALERT; TestPoint_Pad_D1.5mm
TP2: PACK+; TestPoint_Pad_D1.5mm
TP3: GND; TestPoint_Pad_D1.5mm
TP4: BAT-; TestPoint_Pad_D1.5mm
TP5: SERVO+; TestPoint_Pad_D1.5mm
TP6: SDA; TestPoint_Pad_D1.5mm
TP7: SCL; TestPoint_Pad_D1.5mm
TP8: IMON; TestPoint_Pad_D1.5mm
U1: BQ76922; Texas_RSN_WQFN-32-1EP_4x4mm_P0.4mm_EP2.8x2.8mm_ThermalVias; MPN TI BQ76922RSNR
U2: TPS48111-Q1; TI_DGX0019A_VSSOP-19; MPN TI TPS48111LQDGXRQ1

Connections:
+3V3_HOST: J9.1, R10.2, R37.2, R40.2
/BQ_CHG: R17.1, U1.31 (CHG)
/BQ_DSG: D4.1 (K), R19.1, U1.30 (DSG)
/BQ_LD: R16.1, U1.28 (LD)
/BQ_PACK: R15.1, U1.29 (PACK)
/ESTOP_N: J11.3, J12.6, R40.1
/ESTOP_RET: J11.2, R30.1
/KILL: J12.1, R12.1
/PWR_INT_N: D2.2 (A), J12.4, R10.1
/RAIL_V: C23.1, J12.5, R38.2, R39.1
/SCL: J9.4, R13.1, TP7.1
/SDA: J9.3, R14.1, TP6.1
/SERVO_EN: J12.2, R32.1
/SERVO_FLT_N: J12.8, R37.1, U2.4 (~FLT_T), U2.5 (~FLT_I)
/SERVO_IMON: C20.1, J12.7, R36.1, TP8.1, U2.7 (IMON)
BAT+: D1.2 (A), F1.1, J1.2
BAT-: C1.2, C2.2, C4.2, C5.2, C6.2, C11.2, J1.1, R1.1, R7.1, R11.2, R42.2, RT1.2, TP4.1, U1.10 (VSS), U1.19 (CFETOFF), U1.20 (DFETOFF), U1.23 (REGIN), U1.24 (BREG), U1.25 (FUSE), U1.33 (PAD)
GND: C13.2, C14.2, C16.2, C18.2, C19.2, C20.2, C21.2, C22.2, C23.2, C25.2, C27.2, C28.2, D7.2 (A), D8.2 (A), D9.2 (A), J3.2, J4.3, J5.3, J6.3, J7.3, J8.3, J9.2, J10.2, J11.4, J12.3, Q5.2 (E), R1.2, R8.1, R31.2, R33.2, R34.2, R35.2, R36.2, R39.2, R41.2, TP3.1, U2.2 (INP_G), U2.6 (GND)
unnamed: C12.2, C13.1
unnamed: C16.1, R28.2
unnamed: C24.2, C25.1
unnamed: C26.2, C27.1
unnamed: D1.1 (K), R2.1
unnamed: D2.1 (A), R9.2
unnamed: D2.3 (K), J10.1
unnamed: D3.2 (A), F1.2, Q1.1 (S), Q1.2 (S), Q1.3 (S), R18.2
unnamed: D3.1 (K), Q1.4 (G), R17.2, R18.1
unnamed: D4.2 (A), R20.2
unnamed: D5.1 (K), Q2.4 (G), Q4.3 (D), R19.2, R20.1, R21.1
unnamed: D6.1 (K), Q4.1 (G), R22.2, R23.1
unnamed: D7.1 (K), R23.2
unnamed: D10.1 (K), Q3.4 (G), R43.1
unnamed: J2.1, R3.1, R42.1
unnamed: J2.2, R4.1
unnamed: J2.3, R5.1
unnamed: J2.4, R6.1
unnamed: F2.2, J3.1
unnamed: J4.1, J5.1, J6.1, J7.1, J8.1
unnamed: J11.1, R29.2
unnamed: Q1.5 (D), Q2.5 (D)
unnamed: C15.2, Q3.5 (D), R24.2, U2.17 (CS-)
unnamed: C28.1, Q5.1 (B), Q5.3 (C), U2.10 (DIODE)
unnamed: TP1.1, U1.16 (ALERT)
unnamed: C1.1, C2.1, C3.2, R2.2, U1.1 (BAT)
unnamed: C3.1, U1.32 (CP1)
unnamed: C4.1, U1.15 (REG18)
unnamed: C11.1, R11.1, R12.2, U1.21 (RST_SHUT)
unnamed: R13.2, U1.17 (SCL)
unnamed: R14.2, U1.18 (SDA)
unnamed: C9.2, C10.2, R8.2, U1.12 (SRN)
unnamed: C9.1, C10.1, R7.2, U1.11 (SRP)
unnamed: RT1.1, U1.13 (TS1)
unnamed: R9.1, U1.14 (TS2)
unnamed: C5.1, R3.2, U1.9 (VC0)
unnamed: C6.1, C7.2, R4.2, U1.8 (VC1)
unnamed: C7.1, C8.2, R5.2, U1.3 (VC4A), U1.4 (VC4B), U1.5 (VC3A), U1.6 (VC3B), U1.7 (VC2)
unnamed: C8.1, R6.2, U1.2 (VC5)
unnamed: C17.1, U2.12 (BST)
unnamed: R25.2, U2.18 (CS+)
unnamed: C18.1, R30.2, R31.1, U2.1 (EN/UVLO)
unnamed: R32.2, R33.1, U2.3 (INP)
unnamed: C15.1, R26.2, U2.19 (ISCP)
unnamed: R34.1, U2.8 (IWRN)
unnamed: R27.2, R28.1, R43.2, U2.14 (PD)
unnamed: R27.1, U2.15 (PU)
unnamed: C19.1, R35.1, U2.9 (TMR)
PACK+: C12.1, C14.1, C24.1, C26.1, D5.2 (A), D6.2 (A), D8.1 (K), F2.1, Q2.1 (S), Q2.2 (S), Q2.3 (S), Q4.2 (S), R15.2, R16.2, R21.2, R22.1, R24.1, R25.1, R26.1, R29.1, R41.1, TP2.1, U2.20 (VS)
SERVO+: C17.2, C21.1, C22.1, D9.1 (K), D10.2 (A), J4.2, J5.2, J6.2, J7.2, Q3.1 (S), Q3.2 (S), Q3.3 (S), R38.1, TP5.1, U2.13 (SRC)

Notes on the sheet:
POWER PATH: PACK, FUSE, CHG/DSG FETs (BQ76922EVM topology), SERVO-RAIL SWITCH (TPS48111-Q1), SERVO HEADERS
BQ76922: CELL PROTECTION, BATTERY MONITOR, MAIN SWITCH
CONTROL (to the ESP32), PULL-UPS, TEST POINTS, E-STOP
Rev B, 2026-10-29. Design: docs/design-v6/2026-10-06-power-circuit.md; checks: docs/design-v6/2026-10-07-power-board-verification.md and the 2026-10-24 records (full simulation, pin audit, layout review). J1, F1 and F2 are soldered by hand (DNP). Kelvin-route SRP/SRN (R7, R8) to the pads of R1, and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
